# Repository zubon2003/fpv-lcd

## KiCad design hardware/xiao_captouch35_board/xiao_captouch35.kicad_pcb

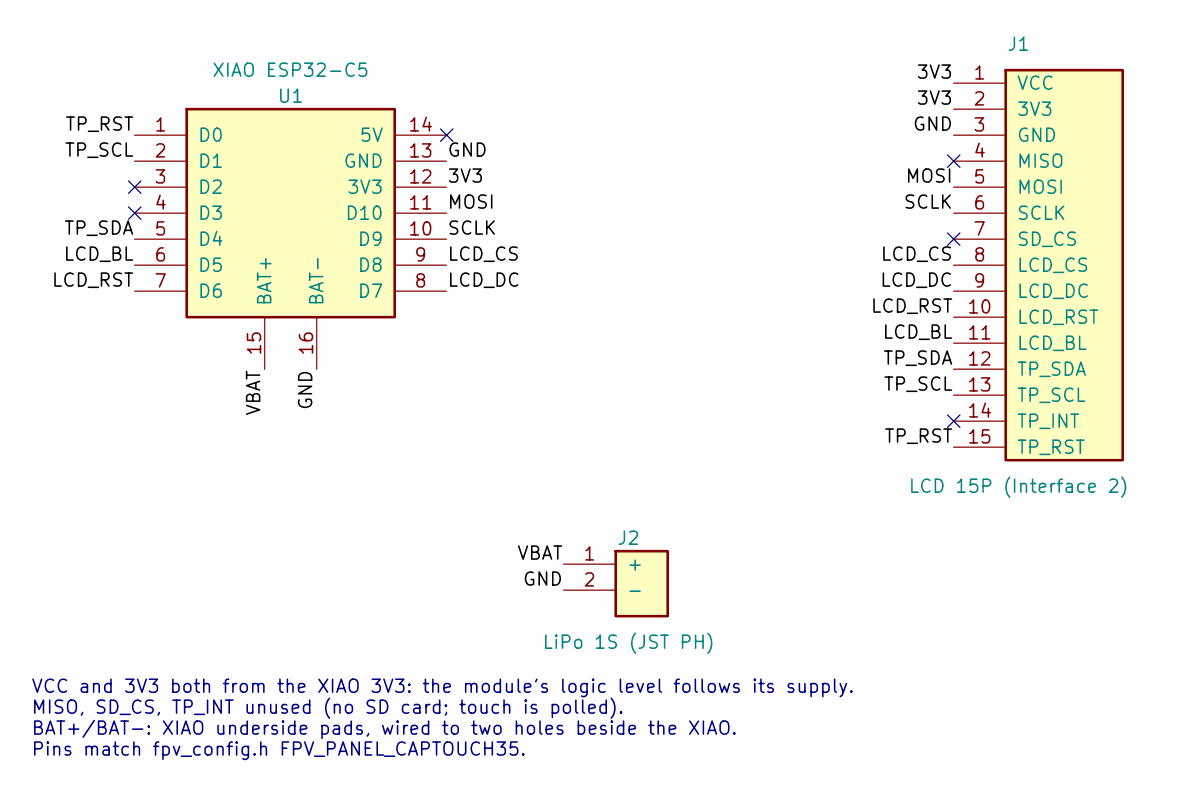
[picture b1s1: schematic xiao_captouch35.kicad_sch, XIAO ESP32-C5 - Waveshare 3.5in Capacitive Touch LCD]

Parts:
J1: LCD 15P (Interface 2); PinHeader_1x15_P2.54mm_Horizontal
J2: LiPo 1S (JST PH); JST_PH_B2B-PH-K_1x02_P2.00mm_Vertical
U1: XIAO ESP32-C5; XIAO_ESP32C5_THT_BAT

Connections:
/3V3: J1.1 (VCC), J1.2 (3V3), U1.12 (3V3)
/GND: J1.3 (GND), J2.2 (-), U1.13 (GND), U1.16 (BAT-)
/LCD_BL: J1.11 (LCD_BL), U1.6 (D5)
/LCD_CS: J1.8 (LCD_CS), U1.9 (D8)
/LCD_DC: J1.9 (LCD_DC), U1.8 (D7)
/LCD_RST: J1.10 (LCD_RST), U1.7 (D6)
/MOSI: J1.5 (MOSI), U1.11 (D10)
/SCLK: J1.6 (SCLK), U1.10 (D9)
/TP_RST: J1.15 (TP_RST), U1.1 (D0)
/TP_SCL: J1.13 (TP_SCL), U1.2 (D1)
/TP_SDA: J1.12 (TP_SDA), U1.5 (D4)
/VBAT: J2.1 (+), U1.15 (BAT+)

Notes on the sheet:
VCC and 3V3 both from the XIAO 3V3: the module's logic level follows its supply. MISO, SD_CS, TP_INT unused (no SD card; touch is polled). BAT+/BAT-: XIAO underside pads, wired to two holes beside the XIAO. Pins match fpv_config.h FPV_PANEL_CAPTOUCH35.

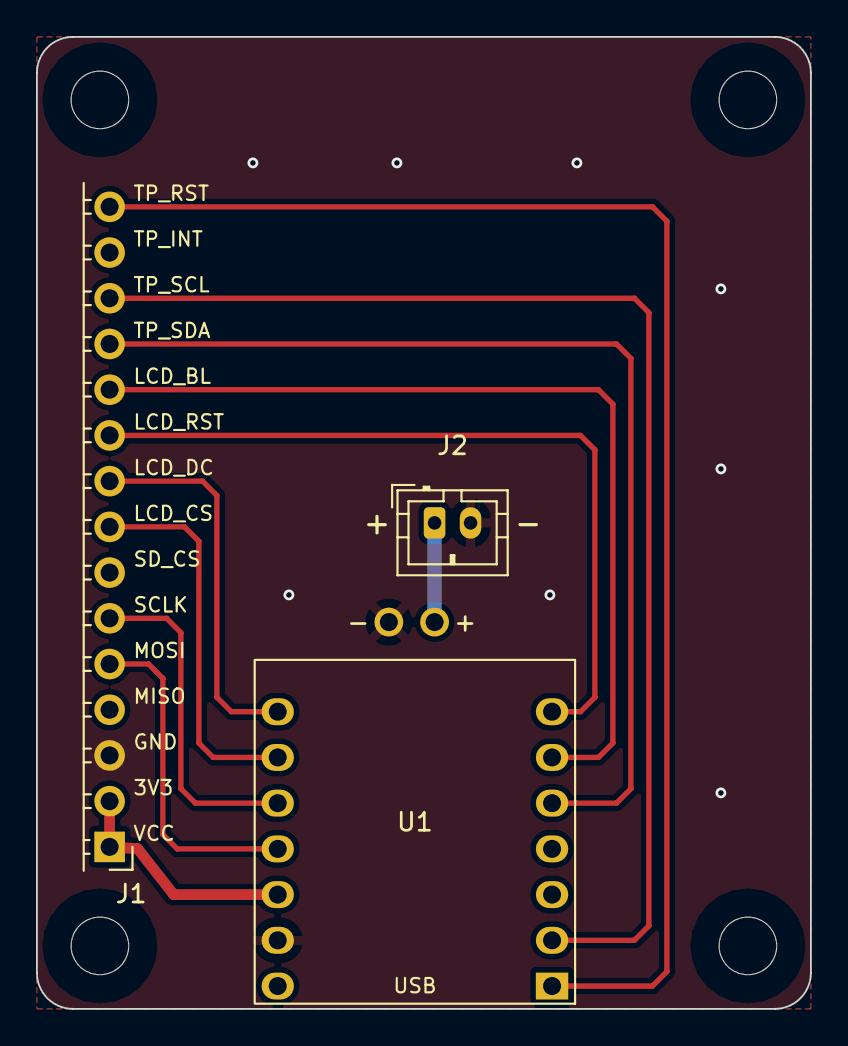
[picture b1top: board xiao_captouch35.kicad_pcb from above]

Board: 2 copper layers, 43.0 x 54.0 mm, 7 parts (0 on the bottom side), 12 nets.

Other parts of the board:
H1, H2, H3, H4: M3; MountingHole_3.2mm_M3

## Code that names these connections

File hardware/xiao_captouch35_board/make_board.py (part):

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
# ------------------------------------------------------------------ pinout
# LCD connector (module "Interface 2", pin 1 first) -> net
LCD_PINS = ["VCC", "3V3", "GND", "MISO", "MOSI", "SCLK", "SD_CS", "LCD_CS", "LCD_DC",
            "LCD_RST", "LCD_BL", "TP_SDA", "TP_SCL", "TP_INT", "TP_RST"]
LCD_NET = {n: n for n in LCD_PINS}
LCD_NET["VCC"] = "3V3"                       # module runs from 3.3 V (logic = supply)
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# XIAO pin number -> (pin name, net). 1..7 = D0..D6, 8..14 = D7, D8, D9, D10,
# 3V3, GND, 5V (Seeed numbering); 15/16 = BAT+/BAT- pads on the underside.
XIAO = {
    1: ("D0", "TP_RST"),     # GPIO1
    2: ("D1", "TP_SCL"),     # GPIO0
    3: ("D2", None),         # GPIO25, strapping
    4: ("D3", None),         # GPIO7, strapping
    5: ("D4", "TP_SDA"),     # GPIO23
    6: ("D5", "LCD_BL"),     # GPIO24
    7: ("D6", "LCD_RST"),    # GPIO11
    8: ("D7", "LCD_DC"),     # GPIO12
    9: ("D8", "LCD_CS"),     # GPIO8
    10: ("D9", "SCLK"),      # GPIO9
    11: ("D10", "MOSI"),     # GPIO10
    12: ("3V3", "3V3"),
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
